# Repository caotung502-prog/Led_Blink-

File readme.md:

# Dự án led blink 

## Sơ đồ mạch nguyên lý

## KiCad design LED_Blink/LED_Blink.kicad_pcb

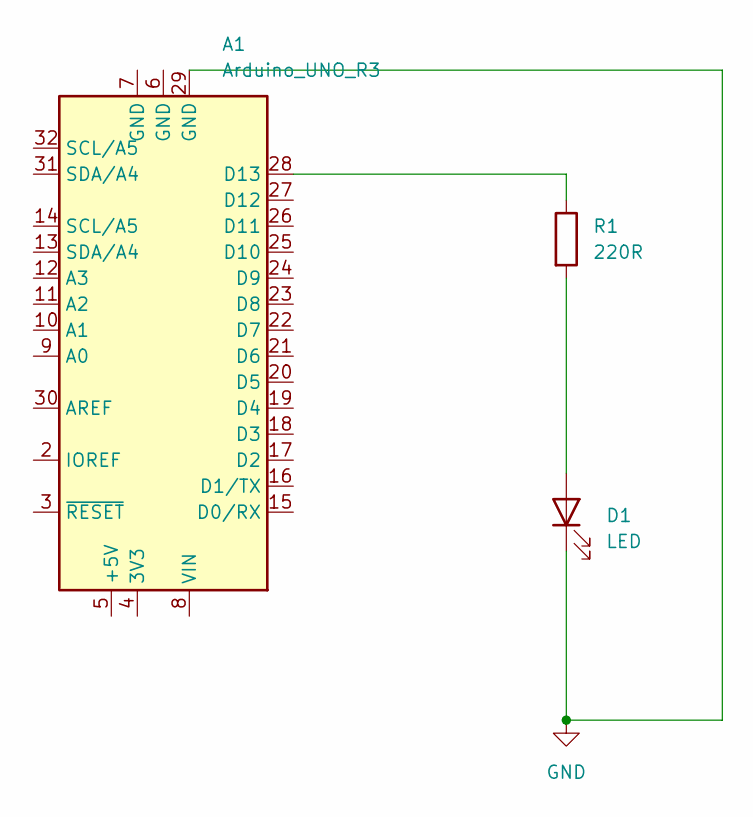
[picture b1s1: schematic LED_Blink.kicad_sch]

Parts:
A1: Arduino_UNO_R3
D1: LED; LED_D5.0mm
R1: 220R; R_Axial_DIN0207_L6.3mm_D2.5mm_P7.62mm_Horizontal

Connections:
GND: A1.29 (GND), D1.1 (K)
unnamed: A1.28 (D13), R1.1
unnamed: D1.2 (A), R1.2

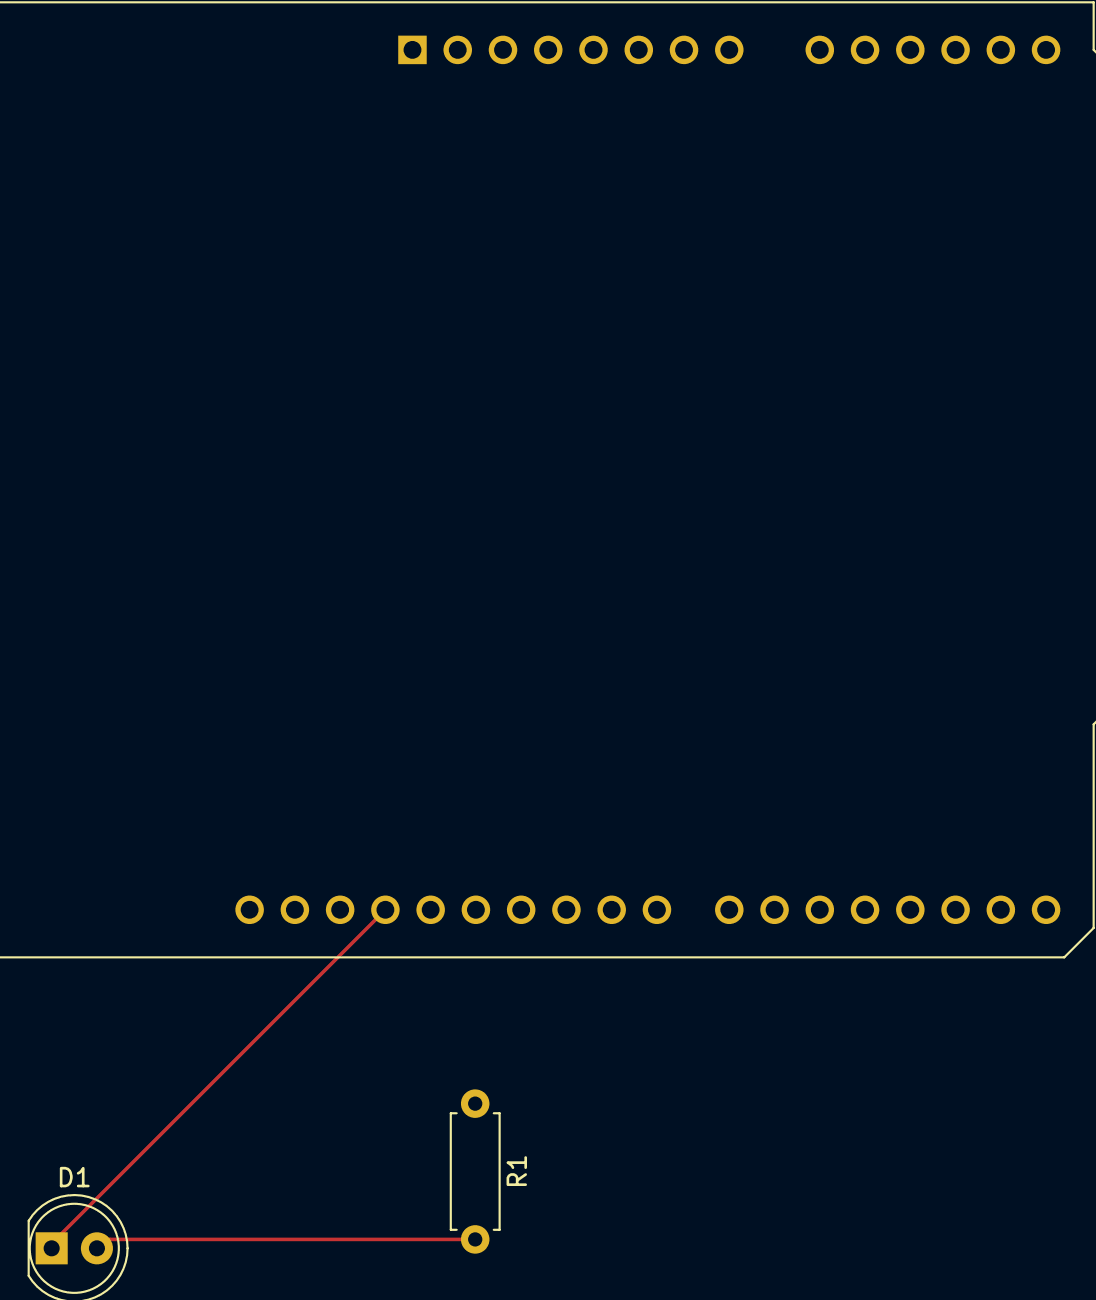
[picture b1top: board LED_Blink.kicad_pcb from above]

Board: 2 copper layers, 3 parts (0 on the bottom side), 3 nets.
